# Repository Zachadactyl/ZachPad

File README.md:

# ZachroPad is here!
I finished v1 of my macropad, and I call it the ZachroPad!

### Inspiration

I wanted to create my own sort of "stream deck" that I could also use for editing photos/videos, gaming, and more. This is perfect for what I want, and it teaches me lots of things. 

### Challenges

This was my first time using KiCAD, and actually designing a circuit board, which was not too much of a challenge but DEFINATELY something totally new. I watched so many tutorials and guides and did a TON of googling. I also pushed lots of random buttons to see if they did what I wanted. Usually not... I am used to Blender 3D so the Fusion 360 keybinds continually annoy me, but I got used to it and managed to crteate something I am incredibly proud of. The tilted "window" for the display took hours and was incredibly frustrating but we got there!

### Specifications

BOM: 
- 9x Cherry MX Switches
- 9x Blank DSA Keycaps (black if available please)
- 1x XIAO RP2040
- 1x 0.91" OLED (GND-VCC-SCL-SDA)
- 1x EC11 Rotary Encoder w/ Switch
- 4x M3x16 Screws
- 4x M3x5x4mm Heatset Inserts
- 9x Through-hole 1N4148 Diodes
- 1x Case (2 parts, BASE and LID, black please)

Others:
- KMK Firmware
- Lid.stl 
- Base.stl

Schematic            |  PCB         |   Case
:-------------------------:|:-------------------------:|:-------------------------:|
    |    |

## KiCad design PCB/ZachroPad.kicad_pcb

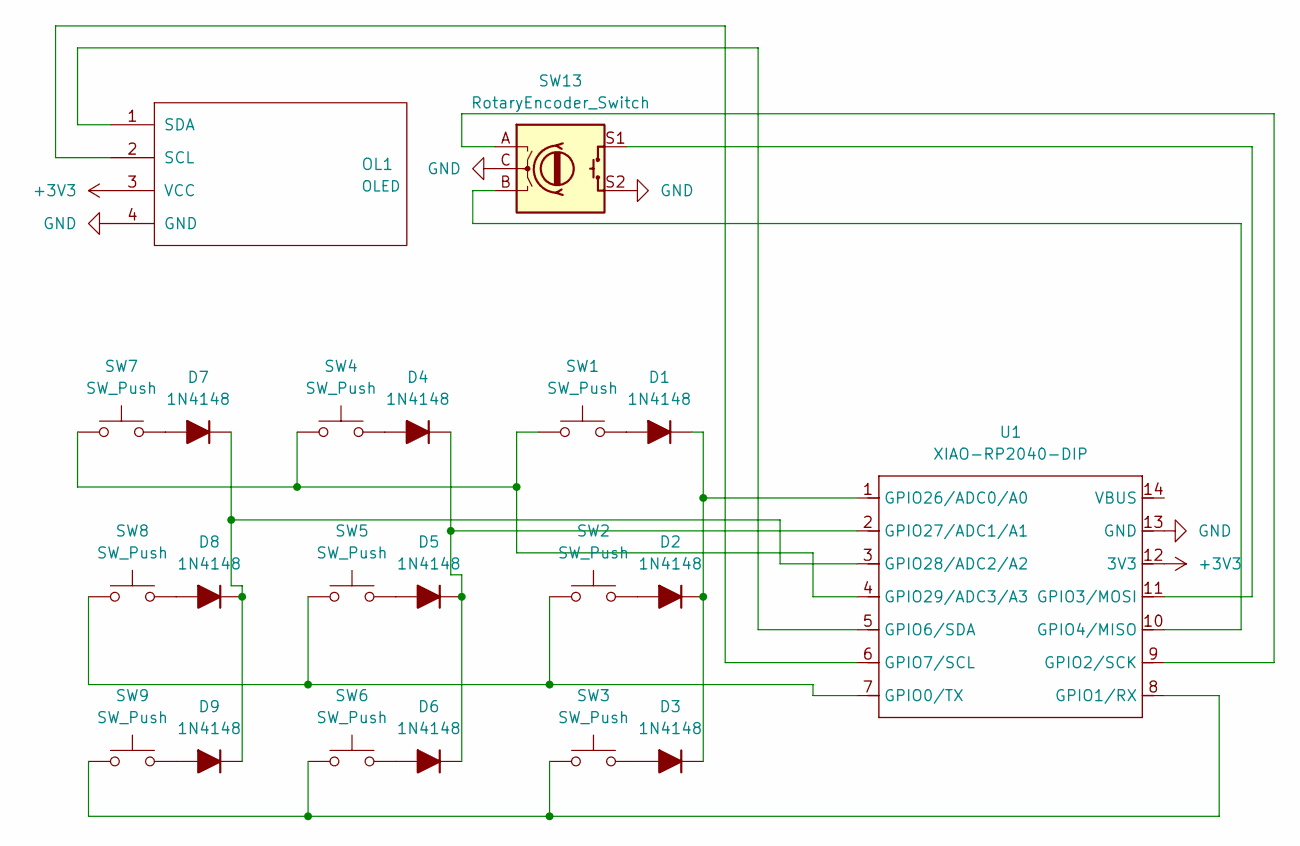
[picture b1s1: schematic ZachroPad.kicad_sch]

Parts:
D1, D2, D3, D4, D5, D6, D7, D8, D9: 1N4148; D_DO-35_SOD27_P7.62mm_Horizontal
OL1: OLED; SSD1306-0.91-OLED-4pin-128x32
SW1, SW2, SW3, SW4, SW5, SW6, SW7, SW8, SW9: SW_Push; SW_Cherry_MX_PCB_1.00u
SW13: RotaryEncoder_Switch; RotaryEncoder_Alps_EC11E-Switch_Vertical_H20mm
U1: XIAO-RP2040-DIP

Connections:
+3V3: OL1.3 (VCC), U1.12 (3V3)
GND: OL1.4 (GND), SW13.C, SW13.S2, U1.13 (GND)
unnamed: D1.2 (A), SW1.2
unnamed: D1.1 (K), D2.1 (K), D3.1 (K), U1.1 (GPIO26/ADC0/A0)
unnamed: D2.2 (A), SW2.2
unnamed: D3.2 (A), SW3.2
unnamed: D4.2 (A), SW4.2
unnamed: D4.1 (K), D5.1 (K), D6.1 (K), U1.2 (GPIO27/ADC1/A1)
unnamed: D5.2 (A), SW5.2
unnamed: D6.2 (A), SW6.2
unnamed: D7.2 (A), SW7.2
unnamed: D7.1 (K), D8.1 (K), D9.1 (K), U1.3 (GPIO28/ADC2/A2)
unnamed: D8.2 (A), SW8.2
unnamed: D9.2 (A), SW9.2
unnamed: OL1.2 (SCL), U1.6 (GPIO7/SCL)
unnamed: OL1.1 (SDA), U1.5 (GPIO6/SDA)
unnamed: SW2.1, SW5.1, SW8.1, U1.7 (GPIO0/TX)
unnamed: SW3.1, SW6.1, SW9.1, U1.8 (GPIO1/RX)
unnamed: SW13.A, U1.9 (GPIO2/SCK)
unnamed: SW13.S1, U1.11 (GPIO3/MOSI)
unnamed: SW13.B, U1.10 (GPIO4/MISO)
unnamed: SW1.1, SW4.1, SW7.1, U1.4 (GPIO29/ADC3/A3)

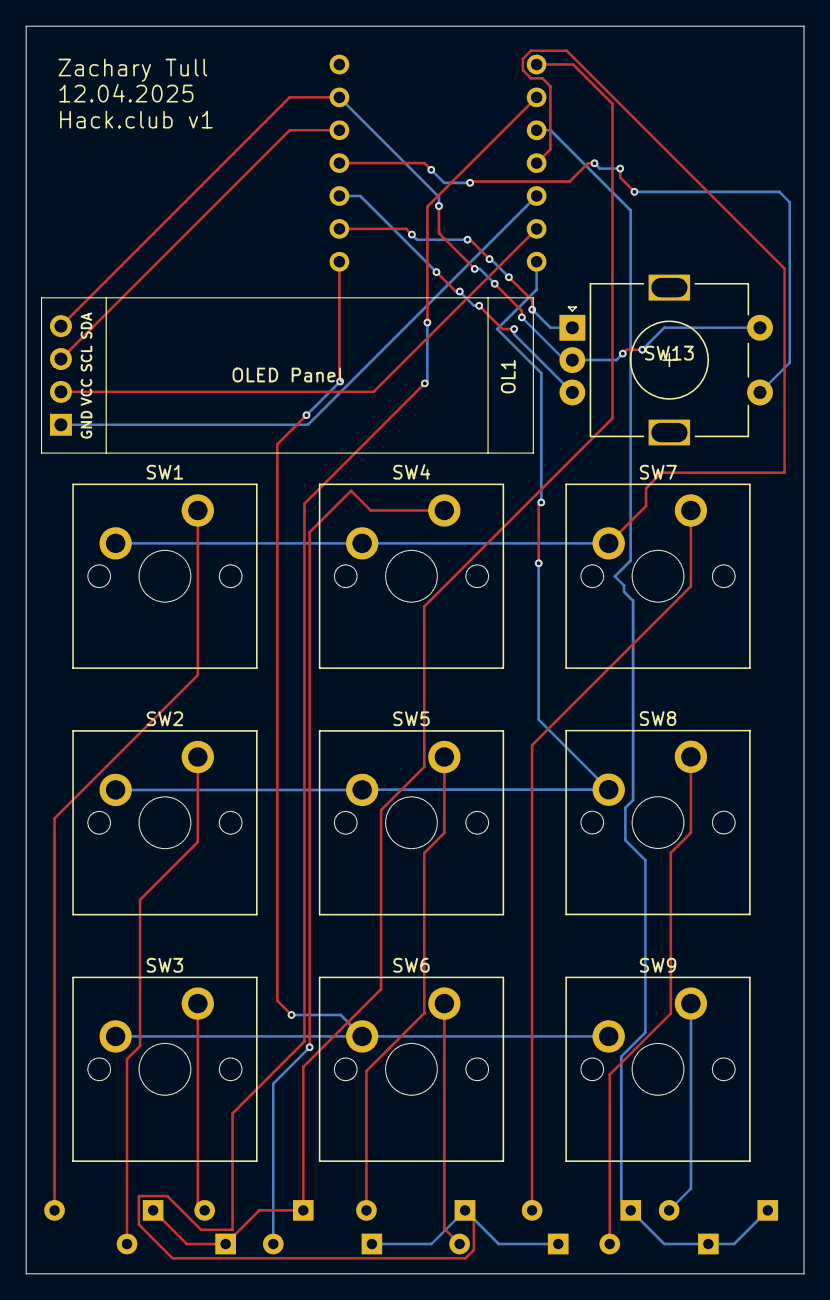
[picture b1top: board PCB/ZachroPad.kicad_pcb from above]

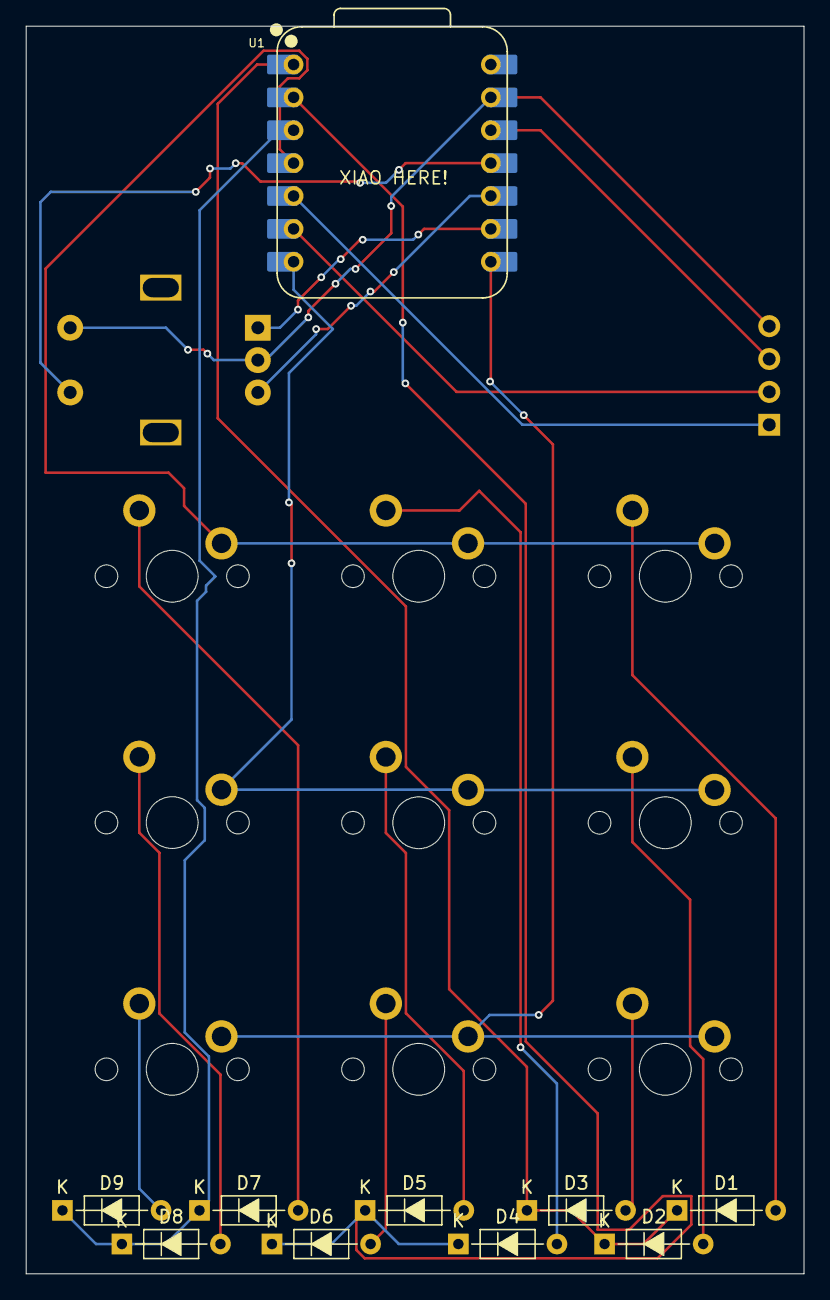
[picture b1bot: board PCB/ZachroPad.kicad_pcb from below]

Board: 2 copper layers, 60.1 x 96.4 mm, 21 parts (10 on the bottom side), 22 nets.

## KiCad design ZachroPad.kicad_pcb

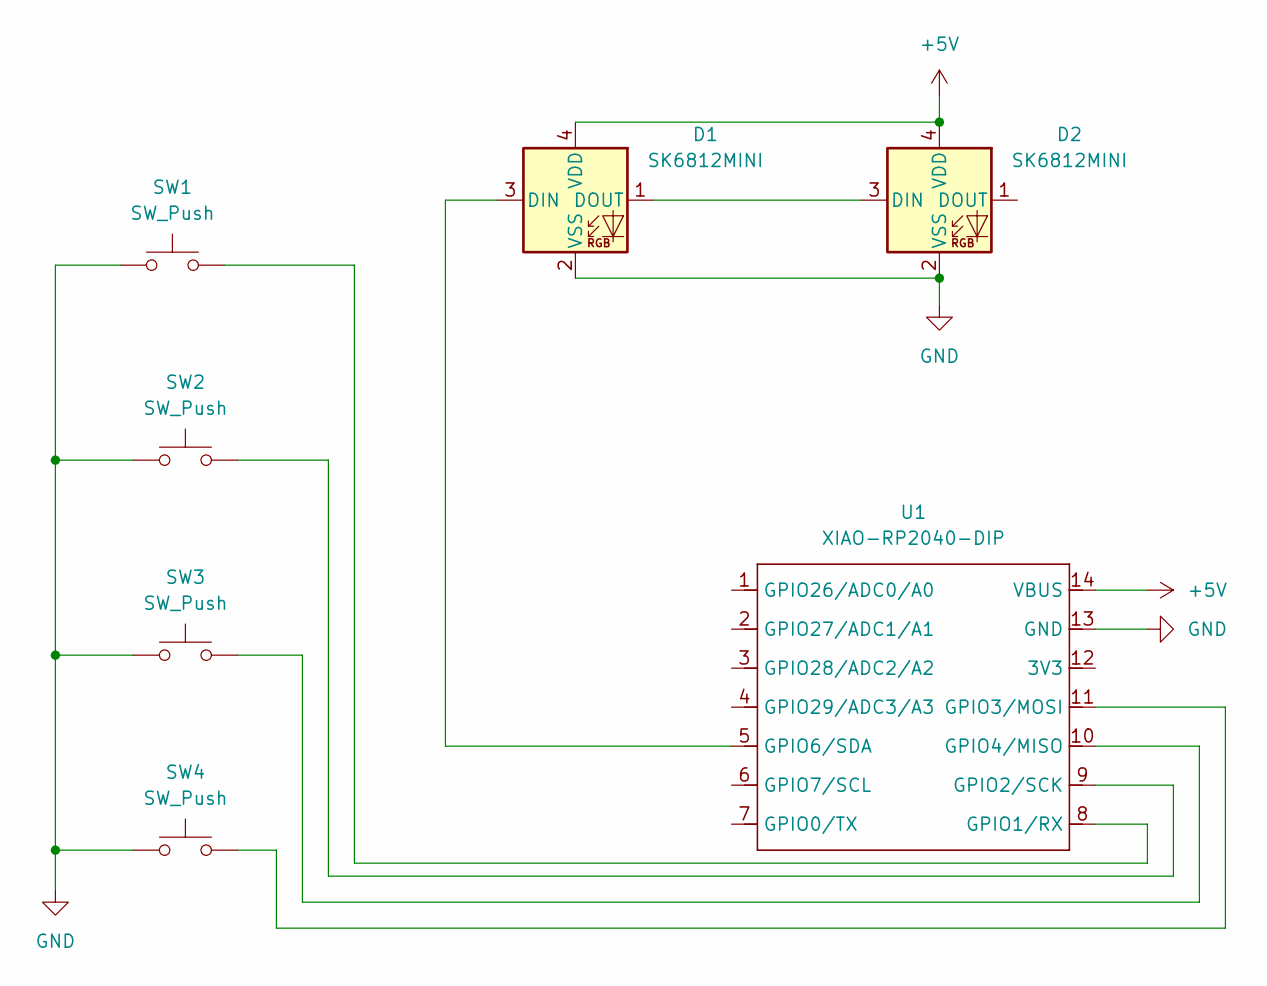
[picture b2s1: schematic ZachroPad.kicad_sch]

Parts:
D1, D2: SK6812MINI; LED_SK6812MINI_PLCC4_3.5x3.5mm_P1.75mm
SW1, SW2, SW3, SW4: SW_Push; SW_Cherry_MX_PCB_1.00u
U1: XIAO-RP2040-DIP

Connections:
+5V: D1.4 (VDD), D2.4 (VDD), U1.14 (VBUS)
GND: D1.2 (VSS), D2.2 (VSS), SW1.1, SW2.1, SW3.1, SW4.1, U1.13 (GND)
unnamed: D1.3 (DIN), U1.5 (GPIO6/SDA)
unnamed: D1.1 (DOUT), D2.3 (DIN)
unnamed: SW1.2, U1.8 (GPIO1/RX)
unnamed: SW2.2, U1.9 (GPIO2/SCK)
unnamed: SW4.2, U1.11 (GPIO3/MOSI)
unnamed: SW3.2, U1.10 (GPIO4/MISO)

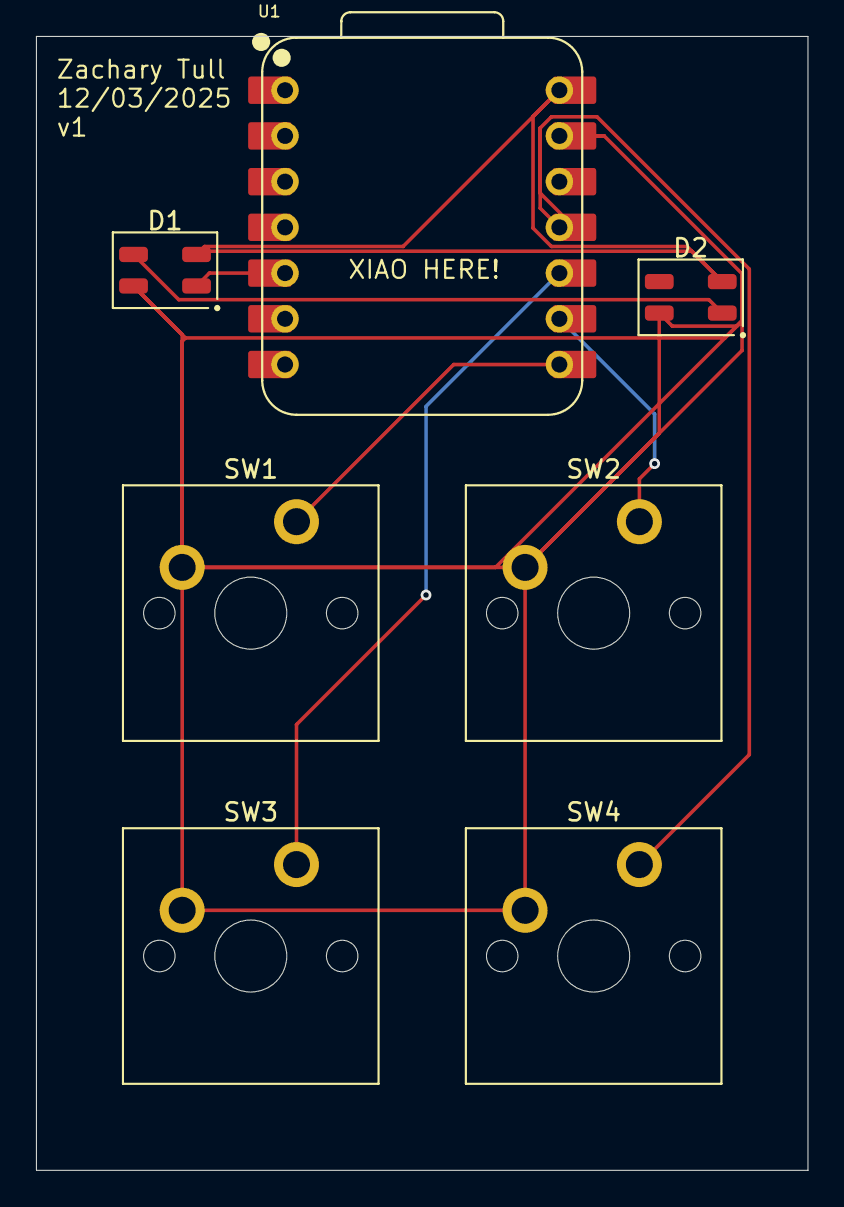
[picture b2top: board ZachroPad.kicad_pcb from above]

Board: 2 copper layers, 42.9 x 63.0 mm, 7 parts (0 on the bottom side), 8 nets.

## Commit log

2025-12-03 Added basic files in no specific layout
2025-12-03 setup2
2025-12-03 placeholders
2025-12-04 Added images
2025-12-04 updates!
2025-12-04 Fixed main image
2025-12-04 Updated images
2025-12-04 Updates case design
2025-12-04 Updated final image
2025-12-04 Added BASE .3mf
2025-12-04 Removed placeholder to show CAD folder
2025-12-04 Added ENTIRE .step file for CAD
2025-12-04 Added LID .3mf
2025-12-04 Fixed README.md link
2025-12-04 Updated basic main.py
2025-12-04 Removed old .txt placeholder
2025-12-05 Updated README.md again
